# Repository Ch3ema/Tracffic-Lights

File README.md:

# Traffic Light Simulator

An Arduino-controlled traffic light, built on a breadboard and then turned into a custom PCB in KiCad.

## What it does

Three LEDs cycle through a standard traffic light sequence.

| Light  | Arduino Pin | Duration |
|--------|-------------|----------|
| Green  | D4          | 3 s      |
| Yellow | D3          | 1 s      |
| Red    | D2          | 3 s      |

## Hardware

- Arduino Uno R3
- 3x 5 mm THT LEDs (red, yellow, green)
- 3x 220 Ω current-limiting resistors
- 1x 4-pin male header (GND + 3 signals)

Each LED anode connects to its Arduino pin through a 220 Ω resistor; all cathodes share a common ground. That gives roughly 14 mA per LED, well under the Uno's 20 mA per-pin limit.

## PCB

Designed in KiCad 10. LEDs grouped at the top, resistors in a row below, 4-pin header at the bottom edge, and four M3 mounting holes at the corners.

Footprints:
- LEDs: `LED_THT:LED_D5.0mm`
- Resistors: `Resistor_THT:R_Axial_DIN0204_L3.6mm_D1.6mm_P5.08mm_Horizontal`
- Header: `Connector_PinHeader_2.54mm:PinHeader_1x04_P2.54mm_Vertical`

## Running it

1. Flash `TrafficLights.ino` to an Arduino Uno
2. Connect the header to the Uno: GND to GND, signals to D2, D3, D4
3. Power over USB

Gerbers are in `/kicad` if you want to fabricate the board.

## Possible improvements

- Pedestrian crossing button with interrupt-driven state change
- Replace blocking `delay()` calls with `millis()` timing so the board can respond to input mid-cycle
- Second light head to simulate a full intersection

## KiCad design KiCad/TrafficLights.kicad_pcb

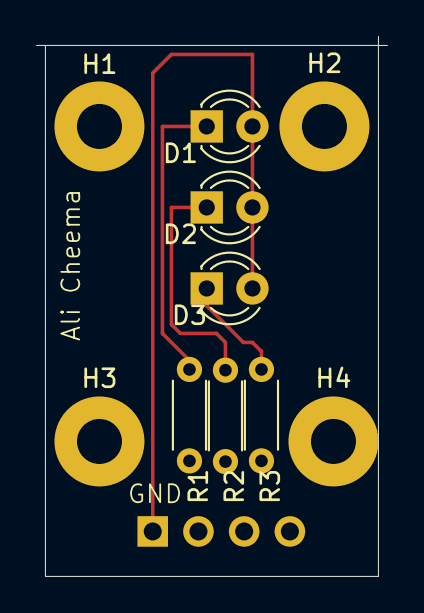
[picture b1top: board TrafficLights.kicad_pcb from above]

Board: 2 copper layers, 19.5 x 30.0 mm, 11 parts (1 on the bottom side), 7 nets.

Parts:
D1, D2, D3: LED; LED_D3.0mm
H1, H2, H3, H4: MountingHole; MountingHole_2.5mm_Pad
J1: Conn_01x04_Pin; PinHeader_1x04_P2.54mm_Horizontal
R1, R2, R3: 220; R_Axial_DIN0204_L3.6mm_D1.6mm_P5.08mm_Horizontal

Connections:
unnamed: D1.2 (A), D2.2 (A), D3.2 (A), J1.1
unnamed: D3.1 (K), R3.2
unnamed: J1.2, R1.1
unnamed: J1.3, R2.1
unnamed: J1.4, R3.1
unnamed: D1.1 (K), R1.2
unnamed: D2.1 (K), R2.2
